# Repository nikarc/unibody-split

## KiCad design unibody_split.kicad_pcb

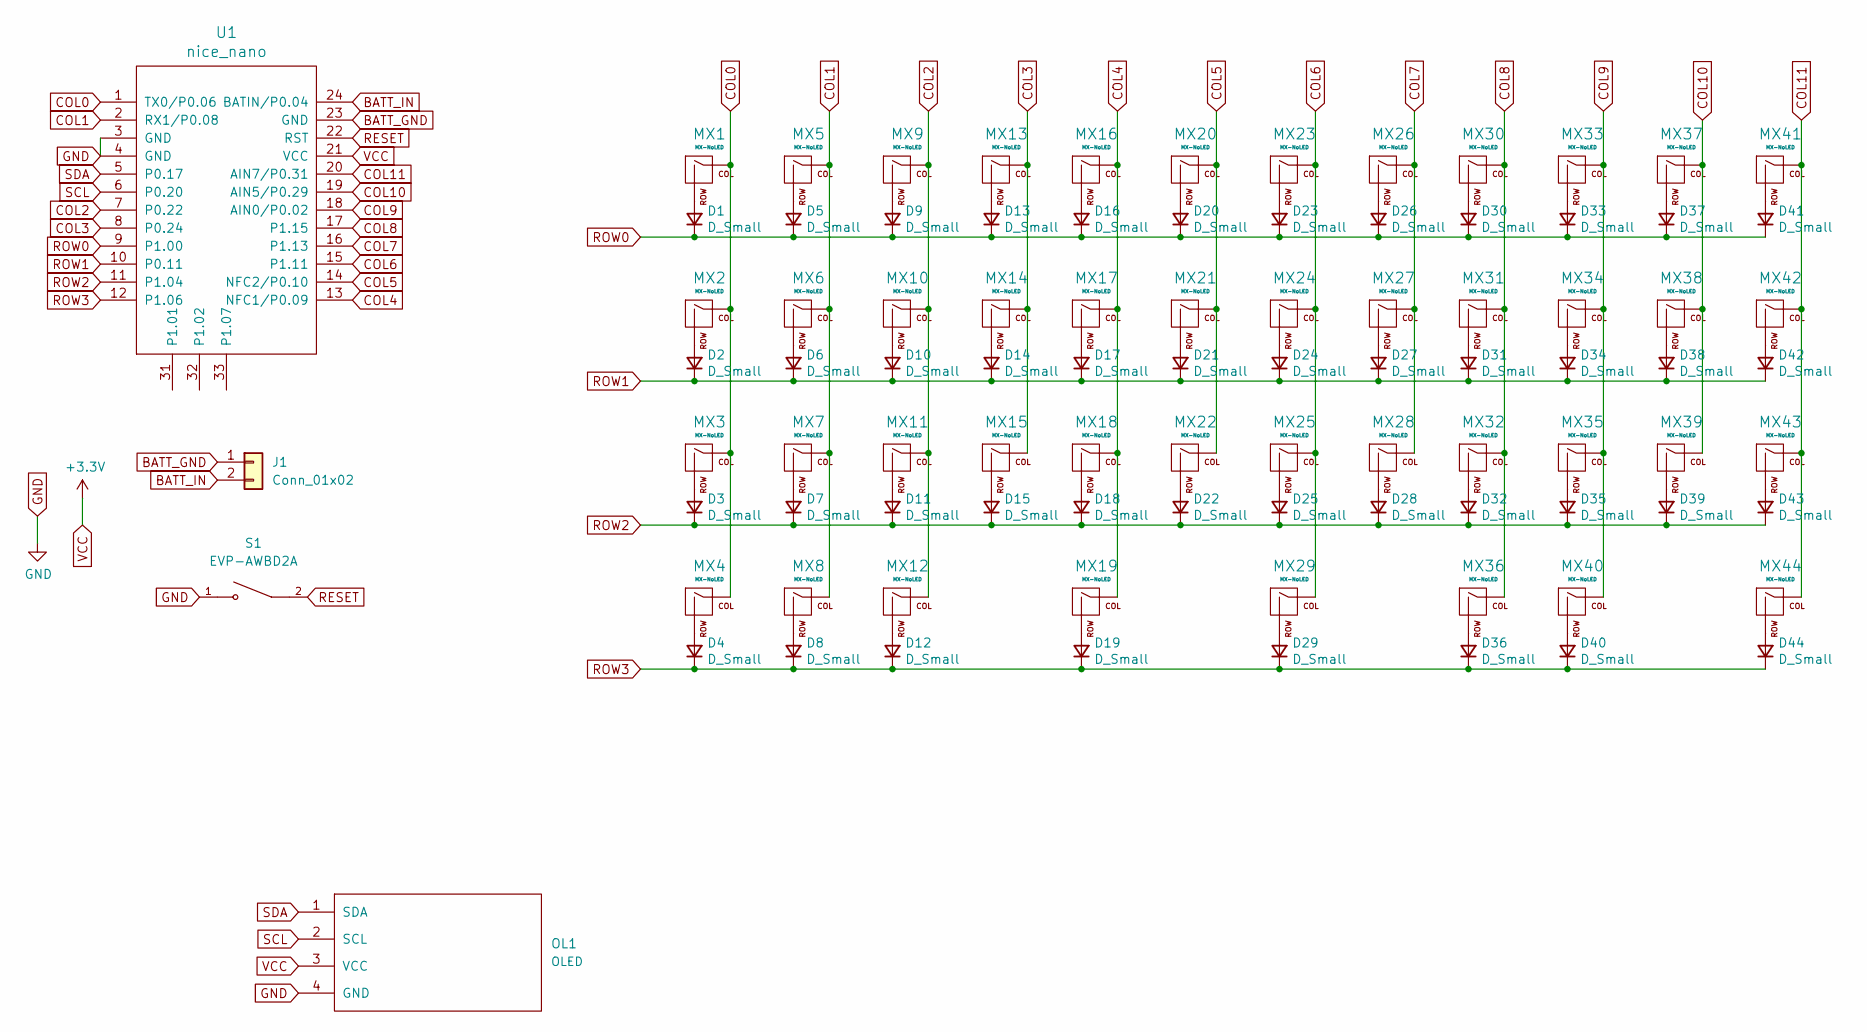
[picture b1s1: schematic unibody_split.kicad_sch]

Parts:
D1, D2, D3, D4, D5, D6, D7, D8, D9, D10, D11, D12, D13, D14, D15, D16, D17, D18, D19, D20, D21, D22, D23, D24, D25, D26, D27, D28, D29, D30, D31, D32, D33, D34, D35, D36, D37, D38, D39, D40, D41, D42, D43, D44: D_Small; D_SMA_Handsoldering
J1: Conn_01x02; JST-2-SMD
MX1, MX5, MX6, MX7, MX9, MX10, MX11, MX13, MX14, MX15, MX16, MX17, MX18, MX20, MX21, MX22, MX23, MX24, MX25, MX26, MX27, MX28, MX30, MX31, MX32, MX33, MX34, MX35, MX37, MX38, MX39, MX43: MX-NoLED; MXOnly-1U-Hotswap
MX2, MX4, MX12, MX36: MX-NoLED; MXOnly-1.25U-Hotswap
MX3, MX41, MX44: MX-NoLED; MXOnly-1.75U-Hotswap
MX8, MX40, MX42: MX-NoLED; MXOnly-1.5U-Hotswap
MX19: MX-NoLED; MXOnly-2.25U-Hotswap
MX29: MX-NoLED; MXOnly-2U-Hotswap
OL1: OLED; OLED_v2
S1: EVP-AWBD2A; SKQG-1155865
U1: nice_nano

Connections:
BATT_GND: J1.1, U1.23 (GND)
BATT_IN: J1.2, U1.24 (BATIN/P0.04)
COL0: MX1.1 (COL), MX2.1 (COL), MX3.1 (COL), MX4.1 (COL), U1.1 (TX0/P0.06)
COL1: MX5.1 (COL), MX6.1 (COL), MX7.1 (COL), MX8.1 (COL), U1.2 (RX1/P0.08)
COL2: MX9.1 (COL), MX10.1 (COL), MX11.1 (COL), MX12.1 (COL), U1.7 (P0.22)
COL3: MX13.1 (COL), MX14.1 (COL), MX15.1 (COL), U1.8 (P0.24)
COL4: MX16.1 (COL), MX17.1 (COL), MX18.1 (COL), MX19.1 (COL), U1.13 (NFC1/P0.09)
COL5: MX20.1 (COL), MX21.1 (COL), MX22.1 (COL), U1.14 (NFC2/P0.10)
COL6: MX23.1 (COL), MX24.1 (COL), MX25.1 (COL), MX29.1 (COL), U1.15 (P1.11)
COL7: MX26.1 (COL), MX27.1 (COL), MX28.1 (COL), U1.16 (P1.13)
COL8: MX30.1 (COL), MX31.1 (COL), MX32.1 (COL), MX36.1 (COL), U1.17 (P1.15)
COL9: MX33.1 (COL), MX34.1 (COL), MX35.1 (COL), MX40.1 (COL), U1.18 (AIN0/P0.02)
COL10: MX37.1 (COL), MX38.1 (COL), MX39.1 (COL), U1.19 (AIN5/P0.29)
COL11: MX41.1 (COL), MX42.1 (COL), MX43.1 (COL), MX44.1 (COL), U1.20 (AIN7/P0.31)
GND: OL1.4 (GND), S1.1, U1.3 (GND), U1.4 (GND)
unnamed: D1.2 (A), MX1.2 (ROW)
unnamed: D2.2 (A), MX2.2 (ROW)
unnamed: D3.2 (A), MX3.2 (ROW)
unnamed: D4.2 (A), MX4.2 (ROW)
unnamed: D5.2 (A), MX5.2 (ROW)
unnamed: D6.2 (A), MX6.2 (ROW)
unnamed: D7.2 (A), MX7.2 (ROW)
unnamed: D8.2 (A), MX8.2 (ROW)
unnamed: D9.2 (A), MX9.2 (ROW)
unnamed: D10.2 (A), MX10.2 (ROW)
unnamed: D11.2 (A), MX11.2 (ROW)
unnamed: D12.2 (A), MX12.2 (ROW)
unnamed: D13.2 (A), MX13.2 (ROW)
unnamed: D14.2 (A), MX14.2 (ROW)
unnamed: D15.2 (A), MX15.2 (ROW)
unnamed: D16.2 (A), MX16.2 (ROW)
unnamed: D17.2 (A), MX17.2 (ROW)
unnamed: D18.2 (A), MX18.2 (ROW)
unnamed: D19.2 (A), MX19.2 (ROW)
unnamed: D20.2 (A), MX20.2 (ROW)
unnamed: D21.2 (A), MX21.2 (ROW)
unnamed: D22.2 (A), MX22.2 (ROW)
unnamed: D23.2 (A), MX23.2 (ROW)
unnamed: D24.2 (A), MX24.2 (ROW)
unnamed: D25.2 (A), MX25.2 (ROW)
unnamed: D26.2 (A), MX26.2 (ROW)
unnamed: D27.2 (A), MX27.2 (ROW)
unnamed: D28.2 (A), MX28.2 (ROW)
unnamed: D29.2 (A), MX29.2 (ROW)
unnamed: D30.2 (A), MX30.2 (ROW)
unnamed: D31.2 (A), MX31.2 (ROW)
unnamed: D32.2 (A), MX32.2 (ROW)
unnamed: D33.2 (A), MX33.2 (ROW)
unnamed: D34.2 (A), MX34.2 (ROW)
unnamed: D35.2 (A), MX35.2 (ROW)
unnamed: D36.2 (A), MX36.2 (ROW)
unnamed: D37.2 (A), MX37.2 (ROW)
unnamed: D38.2 (A), MX38.2 (ROW)
unnamed: D39.2 (A), MX39.2 (ROW)
unnamed: D40.2 (A), MX40.2 (ROW)
unnamed: D41.2 (A), MX41.2 (ROW)
unnamed: D42.2 (A), MX42.2 (ROW)
unnamed: D43.2 (A), MX43.2 (ROW)
unnamed: D44.2 (A), MX44.2 (ROW)
RESET: S1.2, U1.22 (RST)
ROW0: D1.1 (K), D5.1 (K), D9.1 (K), D13.1 (K), D16.1 (K), D20.1 (K), D23.1 (K), D26.1 (K), D30.1 (K), D33.1 (K), D37.1 (K), D41.1 (K), U1.9 (P1.00)
ROW1: D2.1 (K), D6.1 (K), D10.1 (K), D14.1 (K), D17.1 (K), D21.1 (K), D24.1 (K), D27.1 (K), D31.1 (K), D34.1 (K), D38.1 (K), D42.1 (K), U1.10 (P0.11)
ROW2: D3.1 (K), D7.1 (K), D11.1 (K), D15.1 (K), D18.1 (K), D22.1 (K), D25.1 (K), D28.1 (K), D32.1 (K), D35.1 (K), D39.1 (K), D43.1 (K), U1.11 (P1.04)
ROW3: D4.1 (K), D8.1 (K), D12.1 (K), D19.1 (K), D29.1 (K), D36.1 (K), D40.1 (K), D44.1 (K), U1.12 (P1.06)
SCL: OL1.2 (SCL), U1.6 (P0.20)
SDA: OL1.1 (SDA), U1.5 (P0.17)
VCC: OL1.3 (VCC), U1.21 (VCC)

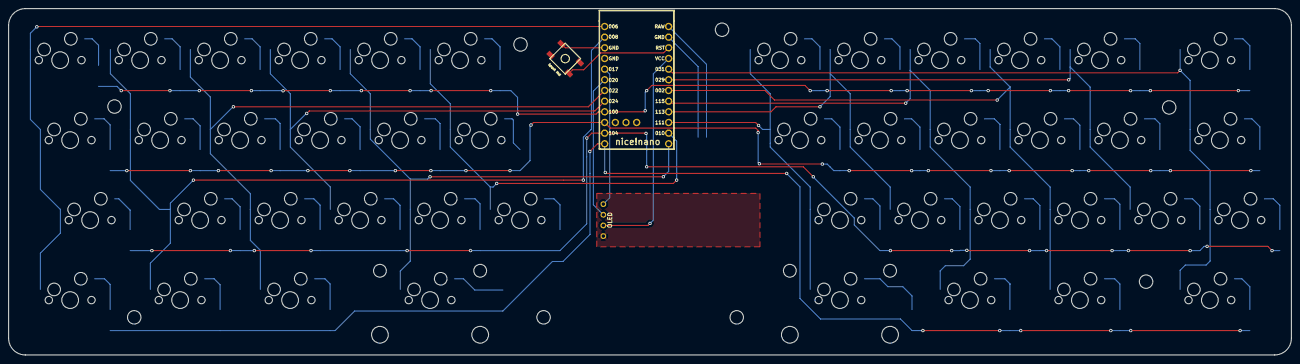
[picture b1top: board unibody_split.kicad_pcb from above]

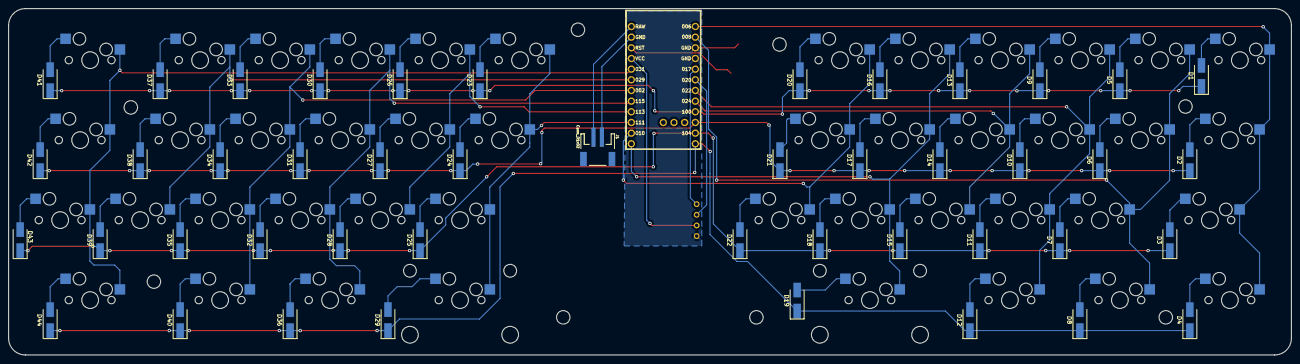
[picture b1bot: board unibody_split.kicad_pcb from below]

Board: 2 copper layers, 305.5 x 82.5 mm, 92 parts (45 on the bottom side), 67 nets.

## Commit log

2022-05-18 Create project
2022-05-18 Adds footprint submodules
2022-05-18 Adds footprint libraries
2022-05-18 Adds nice nano submodule, footprint
2022-05-18 Adds switches, footprints
2022-05-18 PCB layout of switches
2022-05-21 Adds kbd library, wires everything up
2022-05-21 Adds ground plane, fixes edge cuts
2022-05-22 Adds smaller reset switch, JST for battery
2022-05-27 Update JST header to XH
2022-05-27 Use sma diodes
2022-05-27 Uses JST smd
2022-05-28 Moves diodes, edge cuts
2022-05-28 Adds 3d models for switches
2022-05-28 Move nice nano to new board edge, zone fills
2022-05-28 Switch 3d model
2022-05-28 Fixes M29 using wrong footprint
2022-05-28 Adds mounting holes
